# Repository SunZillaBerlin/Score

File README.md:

# SunZilla Score
...is a hard- and software package

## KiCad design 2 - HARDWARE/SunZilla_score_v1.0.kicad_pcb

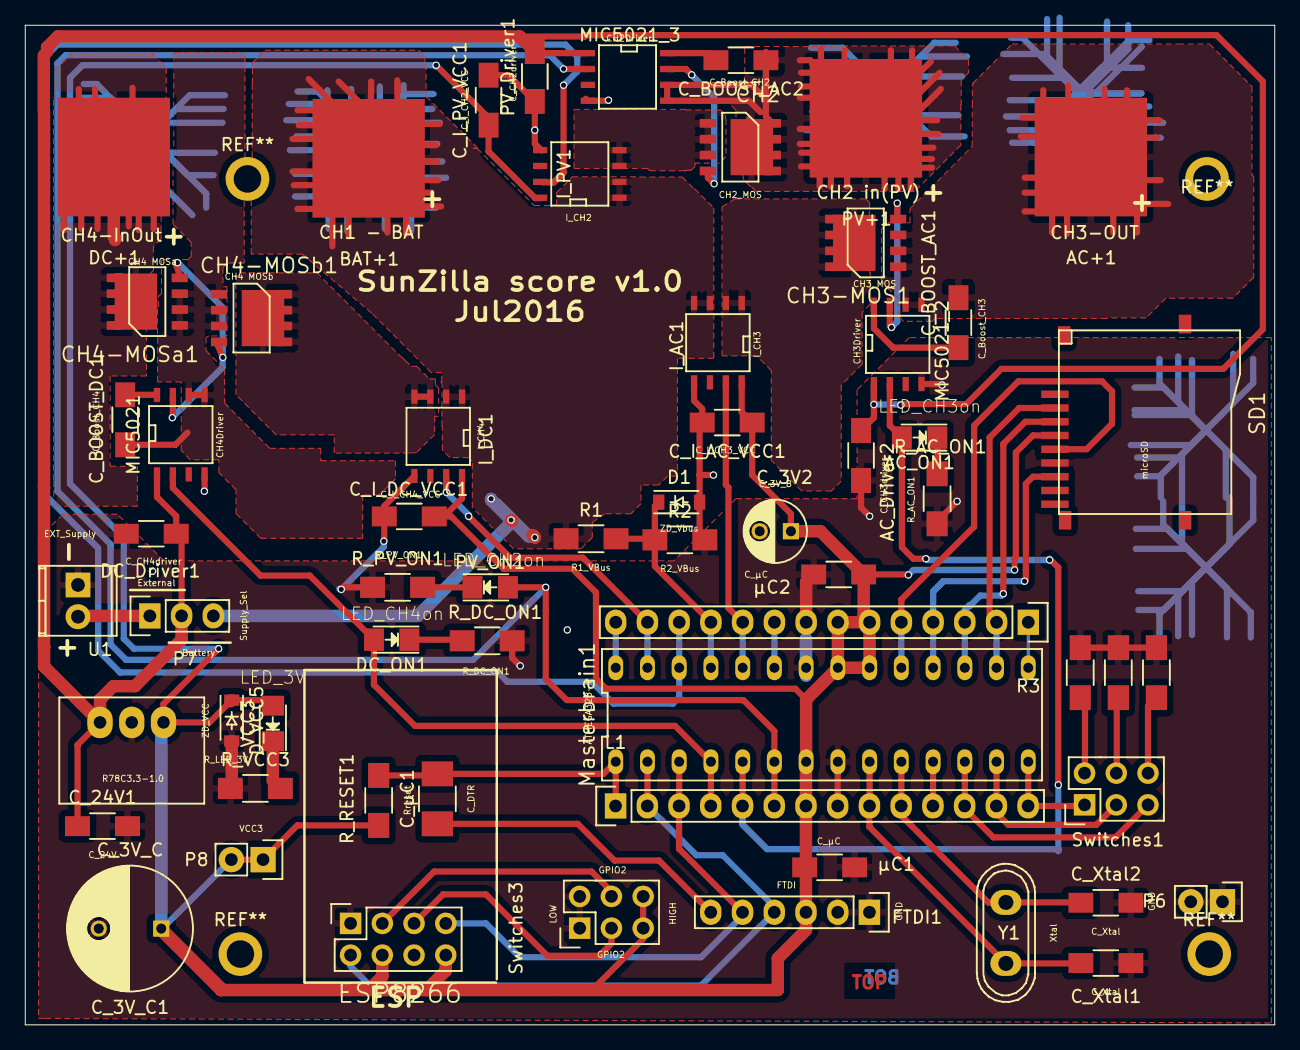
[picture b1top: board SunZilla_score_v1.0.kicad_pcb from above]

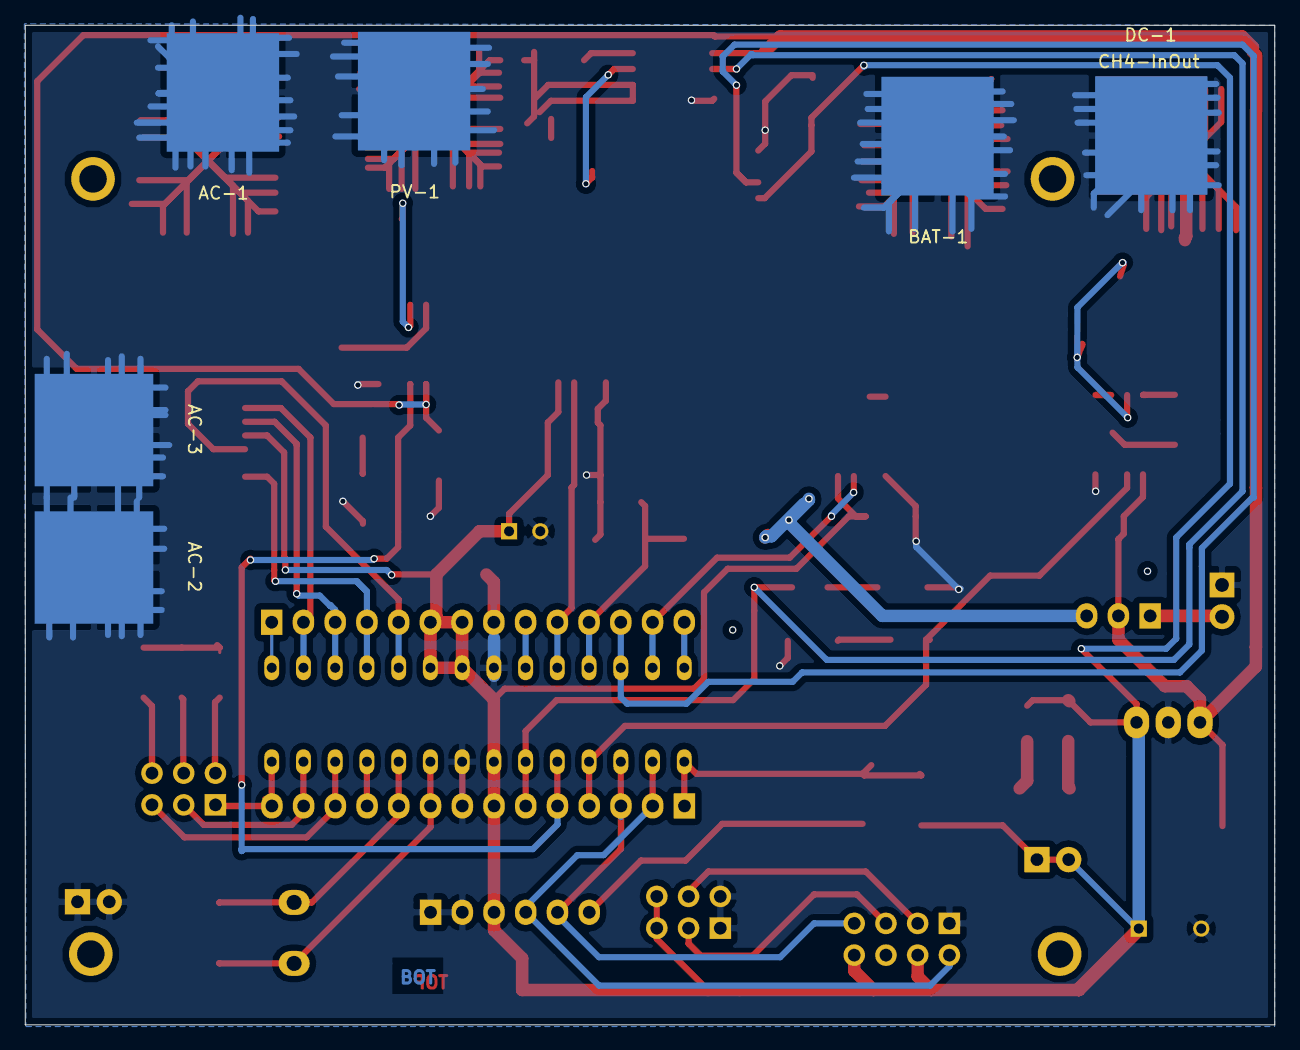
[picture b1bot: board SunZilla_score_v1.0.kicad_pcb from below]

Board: 2 copper layers, 100.0 x 80.0 mm, 67 parts (6 on the bottom side), 51 nets.

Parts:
AC+1: CH3-OUT; Flachsteckzunge_plus
AC-1, AC-2, AC-3: CH3-OUT; Flachsteckzunge_minus
AC_Driver2: C_CH3driver; C_1206_HandSoldering
AC_ON1: LED_CH3on; LED_1206
BAT+1: CH1 - BAT; Flachsteckzunge_plus
BAT-1: CH1 - BAT; Flachsteckzunge_minus
CH2: CH2_MOS; MOSFET_2
CH3-MOS1: CH3 MOS; MOSFET_2
CH4-MOSa1: CH4 MOSa; MOSFET_2
CH4-MOSb1: CH4 MOSb; MOSFET_2
C_3V2: C_3V_B; C_Radial_D5_L11_P2.5
C_3V_C1: C_3V_C; C_Radial_D10_L20_P5
C_24V1: C_24V; C_1206_HandSoldering
C_BOOST_AC1: C_Boost_CH3; C_1206_HandSoldering
C_BOOST_AC2: C_Boost_CH2; C_1206_HandSoldering
C_BOOST_DC1: C_Boost_CH4; C_1206_HandSoldering
C_I_AC_VCC1: C_I_CH3_VCC; C_1206_HandSoldering
C_I_DC_VCC1: C_I_CH4_VCC; C_1206_HandSoldering
C_I_PV_VCC1: C_I_CH2_VCC; C_1206_HandSoldering
C_Xtal1, C_Xtal2: C_Xtal; C_1206_HandSoldering
C_µC1: C_DTR; C_1210_HandSoldering
D1: ZD_Vbus; SOD-123
DC+1: CH4-InOut; Flachsteckzunge_plus
DC-1: CH4-InOut; Flachsteckzunge_minus
DC_Driver1: C_CH4driver; C_1206_HandSoldering
DC_ON1: LED_CH4on; LED_1206
D_VCC5: ZD_VCC; SOD-123
ESP8266: CONN_02X04; Socket_Strip_Straight_2x04
FTDI1: FTDI; Socket_Strip_Straight_1x06
I_AC1: I_CH3; SOIC-8-N
I_DC1: I_CH4; SOIC-8-N
I_PV1: I_CH2; SOIC-8-N
L1: CONN_01X14; Socket_Strip_Straight_1x14
MIC5021: CH4Driver; SOIC-8-N
MIC5021_2: CH3Driver; SOIC-8-N
MIC5021_3: CH2Driver; SOIC-8-N
Masterbrain1: ATMEGA328-P; DIP-28
P5: EXT_Supply; TerminalBlock_Pheonix_MPT-2.54mm_2pol
P6: GND; Pin_Header_Straight_1x02
P7: Supply_Sel; Pin_Header_Straight_1x03
P8: VCC3; Pin_Header_Straight_1x02
PV+1: CH2 in(PV); Flachsteckzunge_plus
PV-1: CH2 in(PV); Flachsteckzunge_minus
PV_Driver1: C_CH2driver; C_1206_HandSoldering
PV_ON1: LED_CH2on; LED_1206
R1: R1_VBus; R_1206_HandSoldering
R2: R2_VBus; R_1206_HandSoldering
R3: CONN_01X14; Socket_Strip_Straight_1x14
R_AC_ON1: R_AC_ON1; R_1206_HandSoldering
R_DC_ON1: R_DC_ON1; R_1206_HandSoldering
R_PV_ON1: R_PV_ON1; R_1206_HandSoldering
R_RESET1: Rreset; R_1206_HandSoldering
R_SW1: R_switch; R_1206_HandSoldering
R_SW2, R_SW3: 16k; R_1206_HandSoldering
R_VCC3: R_LED_3V; R_1206_HandSoldering
SD1: microSD
Switches1, Switches3: Switches; Pin_Header_Straight_2x03
U1: R78C3.3-1.0; DCDC-Conv_Recom_R-78HBxx-0.5
VCC3: LED_3V; LED_1206
Y1: Xtal; Crystal_HC50-U_Vertical
µC1, µC2: C_µC; C_1206_HandSoldering

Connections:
/24V: BAT+1.1, I_AC1.3, I_AC1.4, I_DC1.1, I_DC1.2, I_PV1.1, I_PV1.2, P7.3, R1.1
/A0: Masterbrain1.23, R3.9
/A5: Masterbrain1.28, R3.14
/AC+: CH3-MOS1.5, CH3-MOS1.6, CH3-MOS1.7, CH3-MOS1.8, I_AC1.1, I_AC1.2
/AC_GATE: CH3-MOS1.4, MIC5021_2.7
/AC_GO: AC_ON1.2, L1.5, MIC5021_2.2, Masterbrain1.5
/AC_SOURCE: AC+1.1, CH3-MOS1.1, CH3-MOS1.2, CH3-MOS1.3, C_BOOST_AC1.1, MIC5021_2.5, MIC5021_2.6
/D5: L1.11, Masterbrain1.11
/D9: Masterbrain1.15, R3.1
/DC+: CH4-MOSb1.5, CH4-MOSb1.6, CH4-MOSb1.7, CH4-MOSb1.8, I_DC1.3, I_DC1.4
/DC+_OUT: CH4-MOSa1.5, CH4-MOSa1.6, CH4-MOSa1.7, CH4-MOSa1.8, DC+1.1
/DC_GATE: CH4-MOSa1.4, CH4-MOSb1.4, MIC5021.7
/DC_GO: DC_ON1.2, L1.4, MIC5021.2, Masterbrain1.4
/DC_SOURCE: CH4-MOSa1.1, CH4-MOSa1.2, CH4-MOSa1.3, CH4-MOSb1.1, CH4-MOSb1.2, CH4-MOSb1.3, C_BOOST_DC1.1, MIC5021.5, MIC5021.6
/DTR: C_µC1.1, FTDI1.6
/Ext_24V: P5.2, P7.1
/GND: AC-1.1, AC-2.1, AC-3.1, AC_Driver2.2, BAT-1.1, C_3V2.2, C_3V_C1.2, C_24V1.2, C_I_AC_VCC1.2, C_I_DC_VCC1.2, C_I_PV_VCC1.2, C_Xtal1.2, C_Xtal2.2, D1.2, DC-1.1, DC_Driver1.2, D_VCC5.2, ESP8266.1, FTDI1.1, FTDI1.2, I_AC1.5, I_DC1.5, I_PV1.5, L1.8, MIC5021.4, MIC5021_2.4, MIC5021_3.4, Masterbrain1.8, Masterbrain1.22, P5.1, P6.1, P6.2, PV-1.1, PV_Driver1.2, R2.2, R3.8, R_AC_ON1.1, R_DC_ON1.1, R_PV_ON1.1, R_SW1.2, R_SW2.2, R_SW3.2, R_VCC3.1, SD1.6, Switches3.1, Switches3.2, U1.2, µC1.2, µC2.2
/GPIO0: ESP8266.5, Switches3.3
/GPIO2: ESP8266.3, Switches3.4
/I_AC_3: I_AC1.7, Masterbrain1.24, R3.10
/I_DC_3: I_DC1.7, Masterbrain1.27, R3.13
/I_PV_3: I_PV1.7, Masterbrain1.26, R3.12
/MISO: Masterbrain1.18, R3.4, SD1.7
/MOSI: Masterbrain1.17, R3.3, SD1.3
/PV+: CH2.1, CH2.2, CH2.3, I_PV1.3, I_PV1.4
/PV_GATE: CH2.4, MIC5021_3.7
/PV_GO: L1.6, MIC5021_3.2, Masterbrain1.6, PV_ON1.2
/PV_SOURCE: CH2.5, CH2.6, CH2.7, CH2.8, C_BOOST_AC2.1, MIC5021_3.5, MIC5021_3.6, PV+1.1
/RESET: C_µC1.2, L1.1, Masterbrain1.1, R_RESET1.2
/RX_ATm: ESP8266.2, FTDI1.4, L1.2, Masterbrain1.2
/RX_ESP: ESP8266.7, FTDI1.5, L1.3, Masterbrain1.3
/SCK: Masterbrain1.19, R3.5, SD1.5
/SS: Masterbrain1.16, R3.2, SD1.2
/SW_1: L1.14, Masterbrain1.14, Switches1.1
/SW_2: L1.13, Masterbrain1.13, Switches1.3
/SW_3: L1.12, Masterbrain1.12, Switches1.5
/VCC3: C_3V2.1, C_3V_C1.1, C_I_AC_VCC1.1, C_I_DC_VCC1.1, C_I_PV_VCC1.1, D_VCC5.1, ESP8266.4, ESP8266.8, FTDI1.3, I_AC1.8, I_DC1.8, I_PV1.8, L1.7, Masterbrain1.7, Masterbrain1.20, Masterbrain1.21, P8.1, P8.2, R3.6, R3.7, R_RESET1.1, SD1.4, Switches3.5, Switches3.6, U1.3, VCC3.2, µC1.1, µC2.1
/VCC24: AC_Driver2.1, C_24V1.1, DC_Driver1.1, MIC5021.1, MIC5021_2.1, MIC5021_3.1, P7.2, PV_Driver1.1, U1.1
/V_BUS: D1.1, Masterbrain1.25, R1.2, R2.1, R3.11
/XTal1: C_Xtal1.1, L1.9, Masterbrain1.9, Y1.1
/XTal2: C_Xtal2.1, L1.10, Masterbrain1.10, Y1.2
unnamed: AC_ON1.1, R_AC_ON1.2
unnamed: C_BOOST_AC1.2, MIC5021_2.8
unnamed: C_BOOST_AC2.2, MIC5021_3.8
unnamed: C_BOOST_DC1.2, MIC5021.8
unnamed: DC_ON1.1, R_DC_ON1.2
unnamed: PV_ON1.1, R_PV_ON1.2
unnamed: R_SW1.1, Switches1.2
unnamed: R_SW2.1, Switches1.4
unnamed: R_SW3.1, Switches1.6
unnamed: R_VCC3.2, VCC3.1

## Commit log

2017-01-20 Rename Documentation/index.txt to 1 - DOCUMENTATION/index.txt
2017-01-20 Rename 3 - SOFWARE/ESP8266/incoming_serial.ino to 3 - SOFTWARE/ESP8266/incoming_serial.ino
2017-01-20 Rename 3 - SOFWARE/ESP8266/incoming_wifi.ino to 3 - SOFTWARE/ESP8266/incoming_wifi.ino
2017-01-20 Rename 3 - SOFWARE/ESP8266/print_wifi.ino to 3 - SOFTWARE/ESP8266/print_wifi.ino
2017-01-20 Rename 3 - SOFWARE/ESP8266/score_ESP_v1.4.ino to 3 - SOFTWARE/ESP8266/score_ESP_v1.4.ino
2017-01-20 Rename 3 - SOFWARE/ESP8266/wifi_and_permission.ino to 3 - SOFTWARE/ESP8266/wifi_and_permission.ino
